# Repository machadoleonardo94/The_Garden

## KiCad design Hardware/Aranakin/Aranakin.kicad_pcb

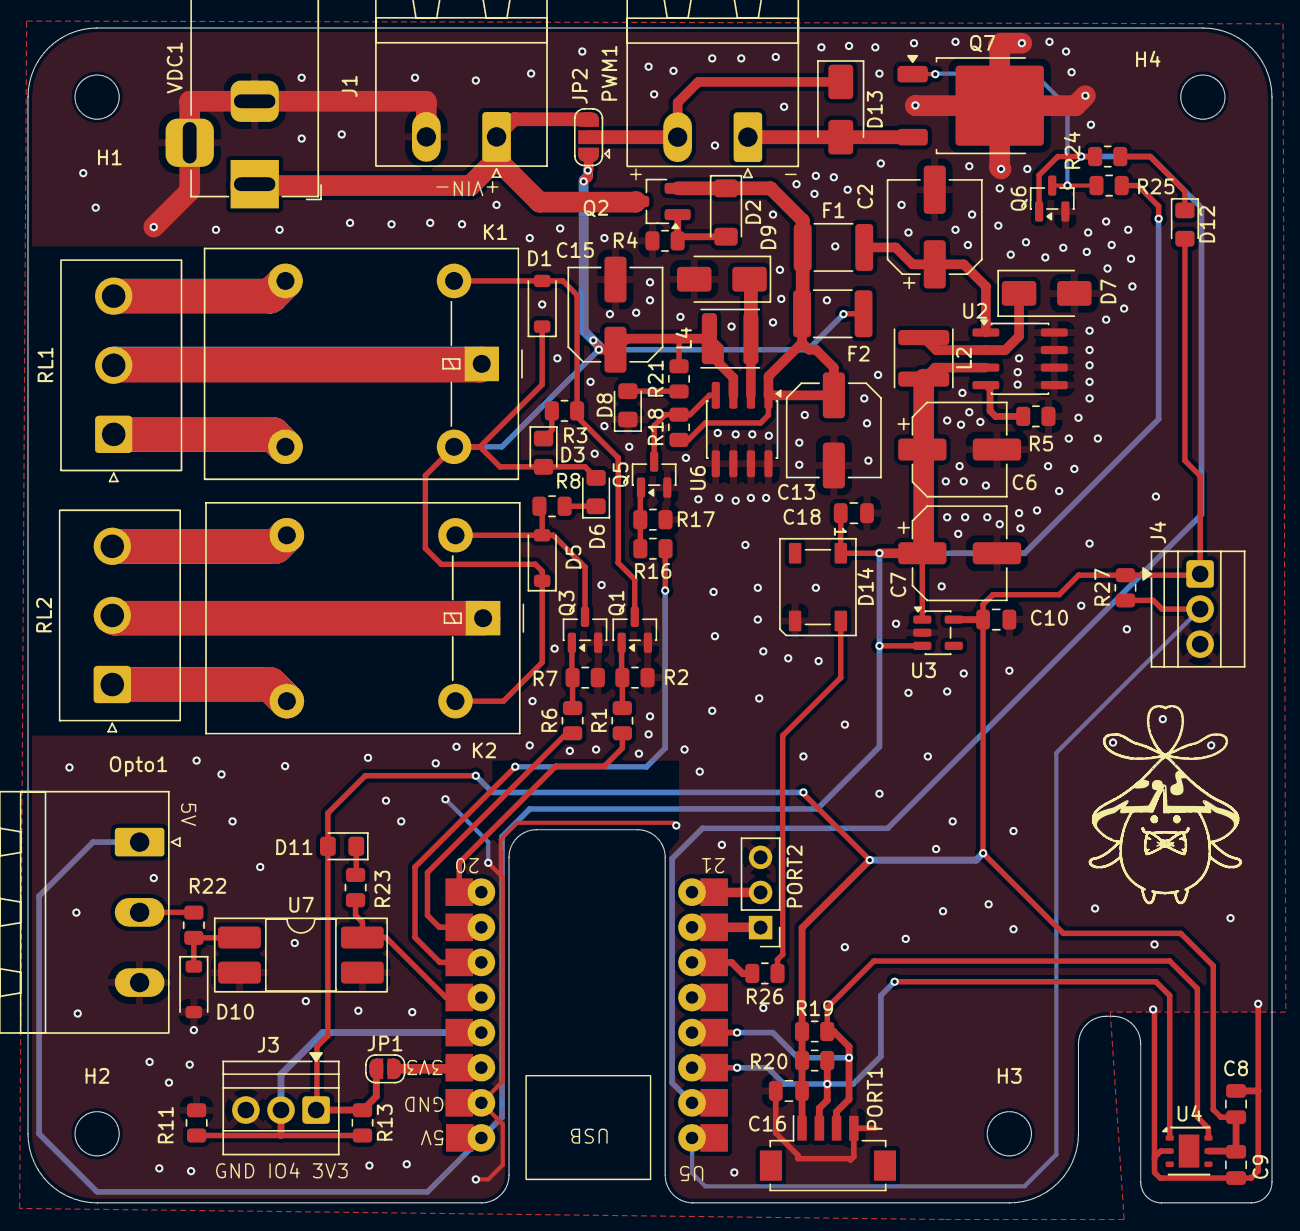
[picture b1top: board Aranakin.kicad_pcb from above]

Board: 2 copper layers, 90.0 x 85.0 mm, 79 parts (0 on the bottom side), 47 nets.

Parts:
C2, C6, C7: 220uF; CP_Elec_6.3x7.7
C8, C10, C16: 10u; C_0805_2012Metric
C9, C18: 100nF; C_0805_2012Metric
C13, C15: 100uF; C_Elec_6.3x7.7
D1, D5, D10: 1N4148W; D_SOD-123
D2: D_Zener; D_MiniMELF
D3, D6: LED_RED; LED_0805_2012Metric_Pad1.15x1.40mm_HandSolder
D7, D9, D13: SS14; D_SMA
D8, D11, D12: LED; LED_0805_2012Metric_Pad1.15x1.40mm_HandSolder
D14: WS2812B; LED_WS2812B_PLCC4_5.0x5.0mm_P3.2mm
F1: 1.1A Polyfuse; Fuse_1812_4532Metric_Pad1.30x3.40mm_HandSolder
F2: Bypass fuse; Fuse_1812_4532Metric_Pad1.30x3.40mm_HandSolder
H1, H2, H3, H4: MountingHole; MountingHole_3.2mm_M3
J1: 5.08-2P-90; PhoenixContact_MSTBA_2,5_2-G-5,08_1x02_P5.08mm_Horizontal
J3: Conn_01x03_Socket; TerminalBlock_Xinya_XY308-2.54-3P_1x03_P2.54mm_Horizontal
J4: 1Wire; TerminalBlock_Xinya_XY308-2.54-3P_1x03_P2.54mm_Horizontal
JP1: SolderJumper_2_Open; SolderJumper-2_P1.3mm_Open_RoundedPad1.0x1.5mm
JP2: SolderJumper_3_Open; SolderJumper-3_P1.3mm_Open_RoundedPad1.0x1.5mm
K1, K2: G5LE-1; Relay_SPDT_Omron-G5LE-1
L2, L4: 33u; L_Sunlord_SWPA4010S
Opto1: Conn_01x03_Pin; PhoenixContact_MSTBA_2,5_3-G-5,08_1x03_P5.08mm_Horizontal
PORT1: Conn_01x04_Socket; Hirose_DF13C_CL535-0404-8-51_1x04-1MP_P1.25mm_Vertical
PORT2: Conn_01x03_Socket; PinHeader_1x03_P2.54mm_Vertical
PWM1: 5.08-2P-90; PhoenixContact_MSTBA_2,5_2-G-5,08_1x02_P5.08mm_Horizontal
Q1, Q3, Q5, Q6: 2N7002K; SOT-23
Q2: PMOS; SOT-23_Handsoldering
Q7: 40N02; TO-252-2
R1, R6, R16, R26: 330; R_0805_2012Metric
R2, R4, R7, R11, R13, R17, R18, R21, R22, R27: 10k; R_0805_2012Metric
R3, R8: 2.2k; R_0805_2012Metric
R5: 100k; R_0805_2012Metric
R19, R20, R25: 2k2; R_0805_2012Metric
R23, R24: 1k; R_0805_2012Metric
RL1, RL2: Conn_01x03_Socket; JST_NV_B03P-NV_1x03_P5.00mm_Vertical
U2: XL1509-5.0; SOIC-8_3.9x4.9mm_P1.27mm
U3: AP2112K-3.3; SOT-23-5
U4: HDC1080; Texas_PWSON-N6
U5: ESP32-C3-Supermini
U6: XL1509-12E1; SOIC-8_3.9x4.9mm_P1.27mm
U7: PC817XI; DIP-4_W8.89mm_SMDSocket_LongPads
VDC1: Barrel_Jack_Switch; BarrelJack_Horizontal

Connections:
1Wire: J4.2, R27.1, U5.1 (GPIO5)
12V_enable: R16.1, U5.11 (GPIO2)
+3.3V: C8.1, C9.2, C10.1, C16.1, D11.2 (A), D12.2 (A), J3.1, J4.1, JP1.1 (A), PORT1.1, R13.1, R19.1, R20.1, R27.2, U3.5 (VOUT), U4.5 (VCC)
+5V: C6.1, C7.1, C18.1, D14.1 (VDD), L2.2, Opto1.1, R25.1, U2.3 (FB), U3.1 (VIN), U3.3 (EN), U5.16 (5V)
ADC: J3.2, R11.2, R13.2, U5.13 (GPIO4)
GND: C2.2, C6.2, C7.2, C8.2, C9.1, C10.2, C13.2, C15.2, C16.2, C18.2, D7.2 (A), D8.1 (K), D9.2 (A), D10.2 (A), D14.3 (VSS), J1.2, J3.3, J4.3, Opto1.3, PORT1.4, PORT2.3, Q1.2 (S), Q3.2 (S), Q5.2 (S), Q6.2 (S), Q7.2 (S), R2.2, R4.2, R5.2, R7.2, R11.1, R17.2, U2.5 (GND), U2.6 (GND), U2.7 (GND), U2.8 (GND), U3.2 (GND), U4.2 (GND), U5.15 (GND), U6.5 (GND), U6.6 (GND), U6.7 (GND), U6.8 (GND), U7.2, U7.3, VDC1.2, VDC1.3
In0: Opto1.2, R22.1
LED_PIN: R26.1, U5.6 (GPIO10)
unnamed: D1.2 (A), K1.2, Q1.3 (D), R3.1
unnamed: D2.2 (A), Q2.1 (G), R4.1
unnamed: D3.1 (K), R3.2
unnamed: D5.2 (A), K2.2, Q3.3 (D), R8.1
unnamed: D6.1 (K), R8.2
unnamed: D7.1 (K), L2.1, U2.2 (OUT)
unnamed: D8.2 (A), R21.1
unnamed: D9.1 (K), L4.1, U6.2 (OUT)
unnamed: D10.1 (K), R22.2, U7.1
unnamed: D11.1 (K), R23.2
unnamed: D12.1 (K), R24.2
unnamed: D13.2 (A), PWM1.1, Q7.3 (D)
unnamed: D13.1 (K), JP2.2 (C), PWM1.2
unnamed: D14.4 (DIN), R26.2
unnamed: JP1.2 (B), U5.14 (3V3)
unnamed: PORT2.1, U5.7 (GPIO20/U0RXD)
unnamed: PORT2.2, U5.8 (GPIO21/U0TXD)
unnamed: Q1.1 (G), R1.2, R2.1
unnamed: Q3.1 (G), R6.2, R7.1
unnamed: Q5.3 (D), R18.2, U6.4 (~EN)
unnamed: Q5.1 (G), R16.2, R17.1
unnamed: Q6.3 (D), Q7.1 (G), R25.2
unnamed: K1.4, RL1.1
unnamed: K1.1, RL1.2
unnamed: K1.3, RL1.3
unnamed: K2.4, RL2.1
unnamed: K2.1, RL2.2
unnamed: K2.3, RL2.3
unnamed: C2.1, F1.2, U2.1 (VIN)
Opto: R23.1, U5.12 (GPIO3), U7.4
PWR_EN: R5.1, U2.4 (~EN)
RELAY0_PIN: R1.1, U5.9 (GPIO0)
RELAY1_PIN: R6.1, U5.10 (GPIO1)
SCL: PORT1.3, R19.2, U4.6 (SCL), U5.4 (GPIO8)
SDA: PORT1.2, R20.2, U4.1 (SDA), U5.3 (GPIO7)
VCC: C13.1, D2.1 (K), F1.1, F2.1, Q2.2 (S), R18.1, U6.1 (VIN)
Vin: J1.1, JP2.3 (B), Q2.3 (D), VDC1.1
openDrain: Q6.1 (G), R24.1, U5.2 (GPIO6)
relayPWR: C15.1, D1.1 (K), D3.2 (A), D5.1 (K), D6.2 (A), F2.2, JP2.1 (A), K1.5, K2.5, L4.2, R21.2, U6.3 (FB)

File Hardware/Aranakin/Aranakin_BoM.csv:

Reference,Qty,Value,Footprint
"C2,C6,C7",3,220uF,Capacitor_SMD:CP_Elec_6.3x7.7
"C8,C10,C16",3,10u,Capacitor_SMD:C_0805_2012Metric
"C9,C18",2,100nF,Capacitor_SMD:C_0805_2012Metric
"C13,C15",2,100uF,Capacitor_SMD:C_Elec_6.3x7.7
"D1,D5,D10",3,1N4148W,Diode_SMD:D_SOD-123
D2,1,D_Zener,Diode_SMD:D_MiniMELF
"D3,D6",2,LED_RED,LED_SMD:LED_0805_2012Metric_Pad1.15x1.40mm_HandSolder
"D7,D9,D13",3,SS14,Diode_SMD:D_SMA
"D8,D11,D12",3,LED,LED_SMD:LED_0805_2012Metric_Pad1.15x1.40mm_HandSolder
D14,1,WS2812B,LED_SMD:LED_WS2812B_PLCC4_5.0x5.0mm_P3.2mm
F1,1,1.1A Polyfuse,Fuse:Fuse_1812_4532Metric_Pad1.30x3.40mm_HandSolder
F2,1,Bypass fuse,Fuse:Fuse_1812_4532Metric_Pad1.30x3.40mm_HandSolder
"J1,PWM1",2,5.08-2P-90,"Connector_Phoenix_MSTB:PhoenixContact_MSTBA_2,5_2-G-5,08_1x02_P5.08mm_Horizontal"
J3,1,Conn_01x03_Socket,TerminalBlock:TerminalBlock_Xinya_XY308-2.54-3P_1x03_P2.54mm_Horizontal
J4,1,1Wire,TerminalBlock:TerminalBlock_Xinya_XY308-2.54-3P_1x03_P2.54mm_Horizontal
"K1,K2",2,G5LE-1,Relay_THT:Relay_SPDT_Omron-G5LE-1
"L2,L4",2,33u,Inductor_SMD:L_Sunlord_SWPA4010S
Opto1,1,Conn_01x03_Pin,"Connector_Phoenix_MSTB:PhoenixContact_MSTBA_2,5_3-G-5,08_1x03_P5.08mm_Horizontal"
PORT1,1,Conn_01x04_Socket,Connector_Hirose:Hirose_DF13C_CL535-0404-8-51_1x04-1MP_P1.25mm_Vertical
PORT2,1,Conn_01x03_Socket,Connector_PinHeader_2.54mm:PinHeader_1x03_P2.54mm_Vertical
"Q1,Q3,Q5,Q6",4,2N7002K,Package_TO_SOT_SMD:SOT-23
Q2,1,PMOS,Package_TO_SOT_SMD:SOT-23_Handsoldering
Q7,1,40N02,Package_TO_SOT_SMD:TO-252-2
"R1,R6,R16,R26",4,330R,Resistor_SMD:R_0805_2012Metric
"R2,R4,R7,R11,R13,R17,R18,R21,R22,R27",10,10k,Resistor_SMD:R_0805_2012Metric
"R3,R8",2,2.2k,Resistor_SMD:R_0805_2012Metric
R5,1,100k,Resistor_SMD:R_0805_2012Metric
"R19,R20,R25",3,2k2,Resistor_SMD:R_0805_2012Metric
"R23,R24",2,1k,Resistor_SMD:R_0805_2012Metric
"RL1,RL2",2,Conn_01x03_Socket,Connector_JST:JST_NV_B03P-NV_1x03_P5.00mm_Vertical
U2,1,XL1509-5.0,Package_SO:SOIC-8_3.9x4.9mm_P1.27mm
U3,1,AP2112K-3.3,Package_TO_SOT_SMD:SOT-23-5
U4,1,HDC1080,Package_SON:Texas_PWSON-N6
U5,1,ESP32-C3-Supermini,Custom_Footprints:ESP32-C3-Supermini
U6,1,XL1509-12E1,Package_SO:SOIC-8_3.9x4.9mm_P1.27mm
U7,1,PC817XI,Package_DIP:DIP-4_W8.89mm_SMDSocket_LongPads
VDC1,1,Barrel_Jack_Switch,Connector_BarrelJack:BarrelJack_Horizontal

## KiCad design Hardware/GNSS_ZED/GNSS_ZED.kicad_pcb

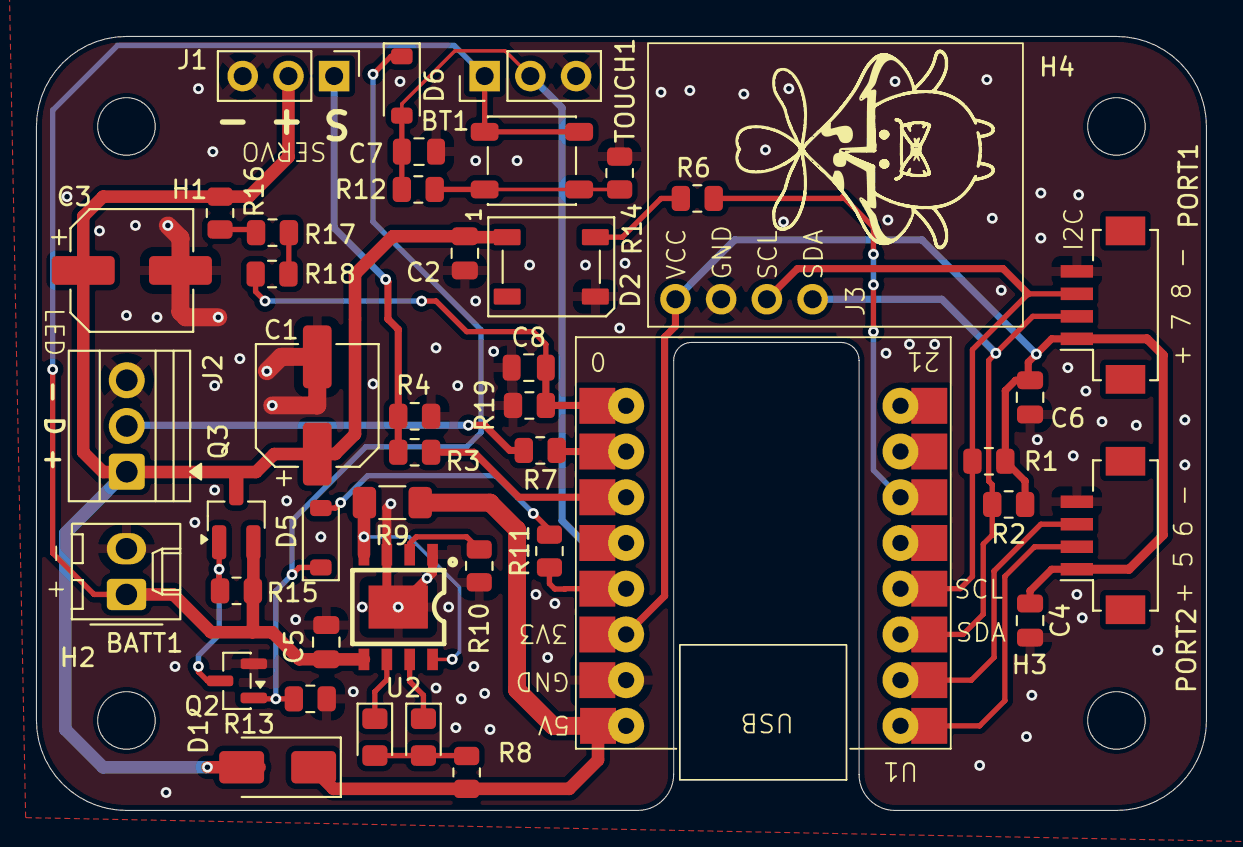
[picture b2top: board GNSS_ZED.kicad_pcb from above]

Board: 2 copper layers, 65.0 x 43.0 mm, 48 parts (0 on the bottom side), 29 nets.

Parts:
BATT1: Conn_01x02_Socket; Molex_KK-254_AE-6410-02A_1x02_P2.54mm_Vertical
BT1: SW_Push; SW_SPST_PTS647_Sx38
C1, C3: 220uF; CP_Elec_6.3x7.7
C2, C7, C8: 100nF; C_0805_2012Metric
C4, C5, C6: 10u; C_0805_2012Metric
D1: SS14; D_SMA
D2: WS2812B; LED_WS2812B_PLCC4_5.0x5.0mm_P3.2mm
D3: LED_BLUE; LED_0805_2012Metric_Pad1.15x1.40mm_HandSolder
D4: LED_RED; LED_0805_2012Metric_Pad1.15x1.40mm_HandSolder
D5, D6: 1N4148W; D_SOD-123
H1, H2, H3, H4: MountingHole; MountingHole_3.2mm_M3
J1: Conn_01x03_Socket; PinHeader_1x03_P2.54mm_Vertical
J2: Conn_01x03_Socket; TerminalBlock_Xinya_XY308-2.54-3P_1x03_P2.54mm_Horizontal
J3: Conn_01x04_Socket; MPU6050
PORT1, PORT2: Conn_01x04_Socket; Hirose_DF13C_CL535-0404-8-51_1x04-1MP_P1.25mm_Vertical
Q2: 2N7002K; SOT-23
Q3: PMOS; SOT-23_Handsoldering
R1, R2, R8, R10, R12: 2.2k; R_0805_2012Metric
R3, R6, R7, R11: 330; R_0805_2012Metric
R4, R13: 10k; R_0805_2012Metric
R9: 0R22; R_1206_3216Metric_Pad1.30x1.75mm_HandSolder
R14, R15, R16, R17, R18, R19: 100k; R_0805_2012Metric
TOUCH1: Conn_01x03_Socket; PinHeader_1x03_P2.54mm_Vertical
U1: ESP32-C3-Supermini
U2: TP4056; ESOP-8_L4.9-W3.9-P1.27-LS6.0-BL-EP

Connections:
+3.3V: C4.1, C6.1, J3.1, PORT1.1, PORT2.1, R1.1, R2.1, U1.14 (3V3)
+5V: D1.1 (K), R8.1, R9.1, U1.16 (5V)
+BATT: BATT1.1, BT1.1, C5.1, Q3.2 (S), R15.2, TOUCH1.1, U2.5 (BAT)
ADC1_0: C8.2, R18.1, R19.1, U1.9 (GPIO0)
Button_GPIO: C7.2, D6.2 (A), R12.2, TOUCH1.2, U1.12 (GPIO3)
GND: BATT1.2, C1.2, C2.2, C3.2, C4.2, C5.2, C6.2, C7.1, C8.1, D2.3 (VSS), J1.3, J2.3, J3.2, PORT1.4, PORT2.4, Q2.2 (S), R4.2, R10.1, R13.2, R14.1, R19.2, TOUCH1.3, U1.15 (GND), U2.1 (TEMP), U2.3 (GND), U2.9 (EP)
GPIO_5: PORT2.2, U1.1 (GPIO5)
GPIO_6: PORT2.3, U1.2 (GPIO6)
unnamed: BT1.2, R12.1, R14.2
unnamed: D2.4 (DIN), R6.2
unnamed: D3.2 (A), D4.2 (A), R8.2
unnamed: D3.1 (K), U2.6 (STDBY#)
unnamed: D4.1 (K), U2.7 (CHRG#)
unnamed: D5.2 (A), R11.2
unnamed: D5.1 (K), D6.1 (K), Q2.1 (G), R13.1
unnamed: J1.1, R3.2, R4.1
unnamed: J2.2, R7.2
unnamed: Q2.3 (D), Q3.1 (G), R15.1
unnamed: R16.1, R17.2
unnamed: R17.1, R18.2
unnamed: R9.2, U2.4 (VCC), U2.8 (CE)
unnamed: R10.2, U2.2 (PROG)
SCL: J3.3, PORT1.3, R1.2, U1.4 (GPIO8)
SDA: J3.4, PORT1.2, R2.2, U1.3 (GPIO7)
Servo_out: R3.1, U1.11 (GPIO2)
Status_LED: R6.1, U1.6 (GPIO10)
Strip_out: R7.1, U1.10 (GPIO1)
V_REG: C1.1, C2.1, C3.1, D1.2 (A), D2.1 (VDD), J1.2, J2.1, Q3.3 (D), R16.2
latch_enable: R11.1, U1.13 (GPIO4)

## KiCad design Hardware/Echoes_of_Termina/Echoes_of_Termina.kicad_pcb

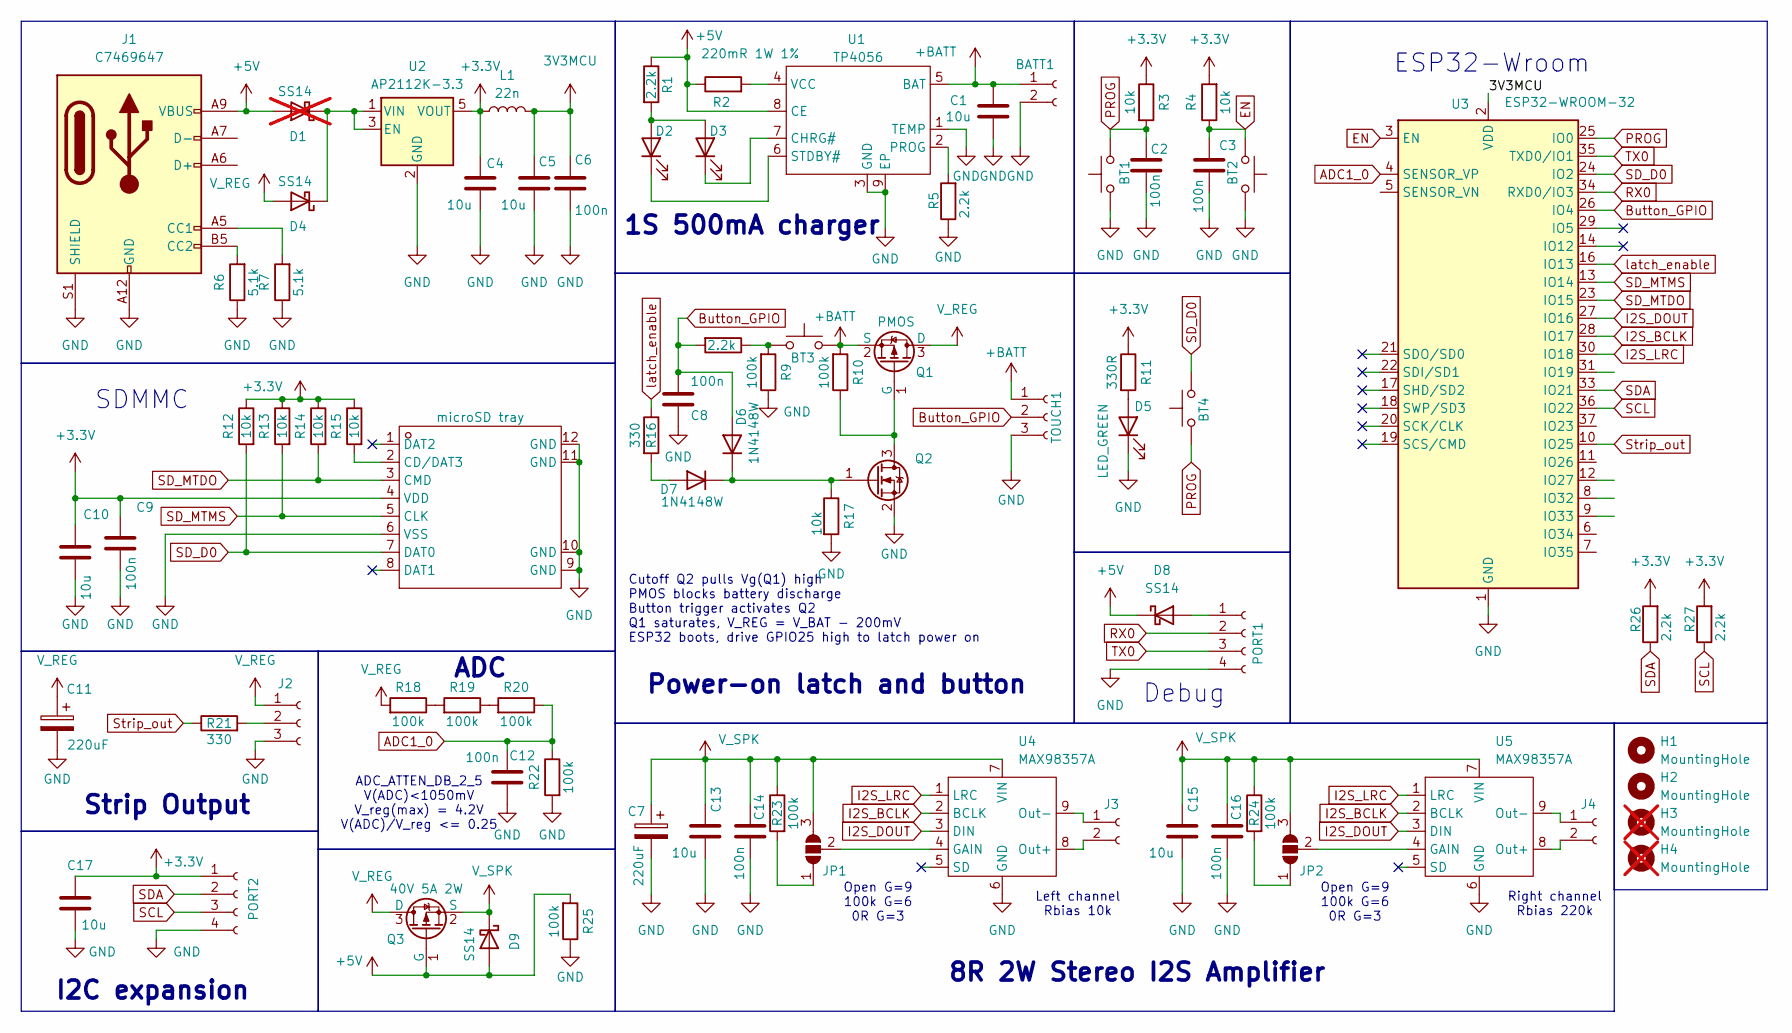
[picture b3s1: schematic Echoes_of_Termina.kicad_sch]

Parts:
BATT1: Conn_01x02_Socket; Molex_KK-254_AE-6410-02A_1x02_P2.54mm_Vertical; LCSC C49023803
BT1, BT2, BT3, BT4: SW_Push; SW_SPST_PTS647_Sx38; LCSC C2888502
C1, C4, C5, C10, C13, C15, C17: 10u; C_0805_2012Metric; LCSC C162422
C2, C3, C6, C9: 100n; C_0805_2012Metric; LCSC C49678
C7, C11: 220uF; CP_Elec_8x10.5; Mfr. Part Number 35TKV220M8X10.5; LCSC C2162971
C8, C12, C14, C16: 100n; C_0805_2012Metric; Mfr. Part Number CC0805KRX7R9BB104; LCSC C49678
D1: SS14; D_SMA; LCSC C2480; not fitted
D2: LED_BLUE; LED_0805_2012Metric_Pad1.15x1.40mm_HandSolder; LCSC C965817
D3: LED_RED; LED_0805_2012Metric_Pad1.15x1.40mm_HandSolder; LCSC C84256
D4, D8, D9: SS14; D_SMA; LCSC C2480
D5: LED_GREEN; LED_0805_2012Metric_Pad1.15x1.40mm_HandSolder; LCSC C84256
D6, D7: 1N4148W; D_SOD-123; Mfr. Part Number 1N4148W-7-F; LCSC C83528
H1, H2: MountingHole; MountingHole_3.2mm_M3
H3, H4: MountingHole; MountingHole_3.2mm_M3; not fitted
J1: USB_C_Receptacle_USB2.0_8P; USB-C-SMD_GT-USB-7101A; LCSC C7469647
J2: Conn_01x03_Socket; TerminalBlock_Xinya_XY308-2.54-3P_1x03_P2.54mm_Horizontal
J3, J4: Conn_01x02_Socket; JST_GH_BM02B-GHS-TBT_1x02-1MP_P1.25mm_Vertical
JP1, JP2: SolderJumper_3_Open; SolderJumper-3_P1.3mm_Open_RoundedPad1.0x1.5mm
L1: 22n; L_0805_2012Metric; LCSC C108962
PORT1, PORT2: Conn_01x04_Socket; Hirose_DF13C_CL535-0404-8-51_1x04-1MP_P1.25mm_Vertical; LCSC C7433470
Q1, Q3: PMOS; SOT-23_Handsoldering; LCSC C42456992
Q2: 2N7002K; SOT-23; LCSC C65189
R1, R5, R8, R26, R27: 2.2k; R_0805_2012Metric; LCSC C17520
R2: 220mR 1W 1%; R_1206_3216Metric_Pad1.30x1.75mm_HandSolder; Mfr. Part Number RLH12FTCR220; LCSC C2683384
R3, R4, R12, R13, R14, R15, R17: 10k; R_0805_2012Metric; LCSC C17414
R6, R7: 5.1k; R_0805_2012Metric; LCSC C27834
R9, R10, R18, R19, R20, R22, R23, R24, R25: 100k; R_0805_2012Metric; LCSC C149504
R11: 330R; R_0805_2012Metric; LCSC C17630
R16, R21: 330; R_0805_2012Metric; LCSC C17630
TF1: microSD tray; TF-SMD_TF-CARD-XG8P-H1.5; LCSC C7529392
TOUCH1: Conn_01x03_Socket; PinHeader_1x03_P2.54mm_Vertical
U1: TP4056; ESOP-8_L4.9-W3.9-P1.27-LS6.0-BL-EP; LCSC Part Name 1A锂电池充电IC
U2: AP2112K-3.3; SOT-23-5; LCSC C51118
U3: ESP32-WROOM-32; ESP32-WROOM-32U; LCSC C2980301
U4, U5: MAX98357A; LCSC C910544

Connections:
3V3MCU: C5.1, C6.1, L1.2, U3.2 (VDD)
+3.3V: C4.1, C9.2, C10.1, C17.1, L1.1, PORT2.1, R3.1, R4.2, R11.1, R12.1, R13.1, R14.1, R15.1, R26.2, R27.2, TF1.4 (VDD), U2.5 (VOUT)
+5V: D1.2 (A), D8.1 (K), D9.2 (A), J1.A9 (VBUS), J1.B9 (VBUS), Q3.1 (G), R1.1, R2.1, R25.2, U1.8 (CE)
+BATT: BATT1.1, BT3.1, C1.1, Q1.2 (S), R10.2, TOUCH1.1, U1.5 (BAT)
ADC1_0: C12.2, R20.1, R22.1, U3.4 (SENSOR_VP)
Button_GPIO: C8.2, D6.2 (A), R8.2, TOUCH1.2, U3.26 (IO4)
EN: BT2.2, C3.1, R4.1, U3.3 (EN)
GND: BATT1.2, BT1.1, BT2.1, C1.2, C2.2, C3.2, C4.2, C5.2, C6.2, C7.2, C8.1, C9.1, C10.2, C11.2, C12.1, C13.2, C14.1, C15.2, C16.1, C17.2, D5.1 (K), J1.A12 (GND), J1.B12 (GND), J1.S1 (SHIELD), J2.3, PORT1.4, PORT2.4, Q2.2 (S), R5.1, R6.1, R7.1, R9.1, R17.2, R22.2, R25.1, TF1.6 (VSS), TF1.9 (GND), TF1.10 (GND), TF1.11 (GND), TF1.12 (GND), TOUCH1.3, U1.1 (TEMP), U1.3 (GND), U1.9 (EP), U2.2 (GND), U3.1 (GND), U3.15 (GND), U3.38 (GND), U3.39 (GND), U4.6 (GND), U5.6 (GND)
I2S_BCLK: U3.28 (IO17), U4.2 (BCLK), U5.2 (BCLK)
I2S_DOUT: U3.27 (IO16), U4.3 (DIN), U5.3 (DIN)
I2S_LRC: U3.30 (IO18), U4.1 (LRC), U5.1 (LRC)
unnamed: BT3.2, R8.1, R9.2
unnamed: D2.2 (A), D3.2 (A), R1.2
unnamed: D2.1 (K), U1.6 (STDBY#)
unnamed: D3.1 (K), U1.7 (CHRG#)
unnamed: D1.1 (K), D4.1 (K), U2.1 (VIN), U2.3 (EN)
unnamed: D5.2 (A), R11.2
unnamed: D6.1 (K), D7.1 (K), Q2.1 (G), R17.1
unnamed: D7.2 (A), R16.2
unnamed: D8.2 (A), PORT1.1
unnamed: J1.A5 (CC1), R7.2
unnamed: J1.B5 (CC2), R6.2
unnamed: J2.2, R21.2
unnamed: J3.1, U4.9 (Out-)
unnamed: J3.2, U4.8 (Out+)
unnamed: J4.1, U5.9 (Out-)
unnamed: J4.2, U5.8 (Out+)
unnamed: JP1.1 (A), R23.2
unnamed: JP1.2 (C), U4.4 (GAIN)
unnamed: JP2.1 (A), R24.2
unnamed: JP2.2 (C), U5.4 (GAIN)
unnamed: Q1.1 (G), Q2.3 (D), R10.1
unnamed: R18.1, R19.2
unnamed: R19.1, R20.2
unnamed: R15.2, TF1.2 (CD/DAT3)
unnamed: R5.2, U1.2 (PROG)
unnamed: R2.2, U1.4 (VCC)
PROG: BT1.2, BT4.2, C2.1, R3.2, U3.25 (IO0)
RX0: PORT1.2, U3.34 (RXD0/IO3)
SCL: PORT2.3, R27.1, U3.36 (IO22)
SDA: PORT2.2, R26.1, U3.33 (IO21)
SD_D0: BT4.1, R12.2, TF1.7 (DAT0), U3.24 (IO2)
SD_MTDO: R14.2, TF1.3 (CMD), U3.23 (IO15)
SD_MTMS: R13.2, TF1.5 (CLK), U3.13 (IO14)
Strip_out: R21.1, U3.10 (IO25)
TX0: PORT1.3, U3.35 (TXD0/IO1)
V_REG: C11.1, D4.2 (A), J2.1, Q1.3 (D), Q3.3 (D), R18.2
V_SPK: C7.1, C13.1, C14.2, C15.1, C16.2, D9.1 (K), JP1.3 (B), JP2.3 (B), Q3.2 (S), R23.1, R24.1, U4.7 (VIN), U5.7 (VIN)
latch_enable: R16.1, U3.16 (IO13)

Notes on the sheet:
Strip Output
Right channel Rbias 220k
Open G=9 100k G=6 0R G=3
Power-on latch and button
8R 2W Stereo I2S Amplifier
ADC_ATTEN_DB_2_5 V(ADC)<1050mV V_reg(max) = 4.2V V(ADC)/V_reg <= 0.25
ADC
SDMMC
Left channel Rbias 10k
I2C expansion
Cutoff Q2 pulls Vg(Q1) high PMOS blocks battery discharge Button trigger activates Q2 Q1 saturates, V_REG = V_BAT - 200mV ESP32 boots, drive GPIO25 high to latch power on
Debug
ESP32-Wroom
1S 500mA charger

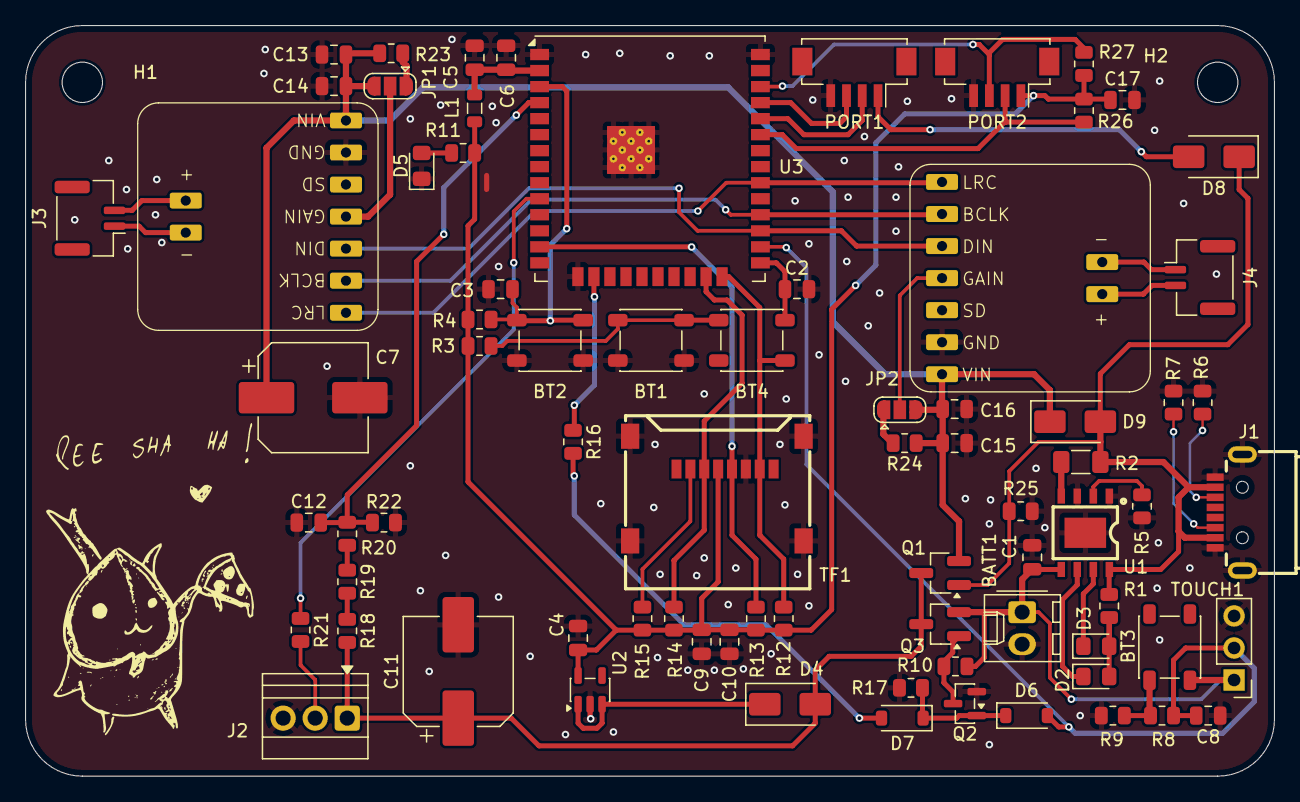
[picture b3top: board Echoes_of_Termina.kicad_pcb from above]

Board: 2 copper layers, 99.0 x 59.5 mm, 78 parts (0 on the bottom side), 49 nets.

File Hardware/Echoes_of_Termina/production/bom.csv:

Designator,Footprint,Quantity,Value,LCSC Part #
"BT1, BT2, BT3, BT4",SW_SPST_PTS647_Sx38,4,SW_Push,C2888502
"C1, C10, C13, C15, C17, C4, C5",0805,7,10u,C162422
"C11, C7",CP_Elec_8x10.5,2,220uF,C2162971
"C12, C14, C16, C2, C3, C6, C8, C9",0805,8,100n,C49678
D2,0805,1,LED_BLUE,C965817
D3,0805,1,LED_RED,C84256
"D4, D8, D9",D_SMA,3,SS14,C2480
D5,0805,1,LED_GREEN,C84256
"D6, D7",D_SOD-123,2,1N4148W,C83528
J1,USB-C-SMD_GT-USB-7101A,1,USB_C_Receptacle_USB2.0_8P,C7469647
J2,TerminalBlock_Xinya_XY308-2.54-3P_1x03_P2.54mm_Horizontal,1,Conn_01x03_Socket,
"J3, J4",JST_GH_BM02B-GHS-TBT_1x02-1MP_P1.25mm_Vertical,2,Conn_01x02_Socket,
L1,0805,1,22n,C108962
"PORT1, PORT2",Hirose_DF13C_CL535-0404-8-51_1x04-1MP_P1.25mm_Vertical,2,Conn_01x04_Socket,C7433470
"Q1, Q3",SOT-23_Handsoldering,2,PMOS,C42456992
Q2,SOT-23,1,2N7002K,C65189
"R1, R26, R27, R5, R8",0805,5,2.2k,C17520
"R10, R18, R19, R20, R22, R23, R24, R25, R9",0805,9,100k,C149504
R11,0805,1,330R,C17630
"R12, R13, R14, R15, R17, R3, R4",0805,7,10k,C17414
"R16, R21",0805,2,330,C17630
R2,1206,1,220mR 1W 1%,C2683384
"R6, R7",0805,2,5.1k,C27834
TF1,TF-SMD_TF-CARD-XG8P-H1.5,1,microSD tray,C7529392
TOUCH1,PinHeader_1x03_P2.54mm_Vertical,1,Conn_01x03_Socket,
U1,ESOP-8_L4.9-W3.9-P1.27-LS6.0-BL-EP,1,TP4056,C382139
U2,SOT-23-5,1,AP2112K-3.3,C51118
U3,ESP32-WROOM-32U,1,ESP32-WROOM-32,C2980301
"U4, U5",MAX98357A,2,MAX98357A,C910544

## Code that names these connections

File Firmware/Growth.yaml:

esphome:
  name: shruberry
  comment: Soil and air monitor node
  friendly_name: Shruberry

esp32:
  board: esp32-c3-devkitm-1
  flash_size: 4MB
  cpu_frequency: 160MHz
  framework:
    type: arduino

# Enable logging
logger:

# Enable Home Assistant API
api:
  encryption:
    key: "RdF1G7t8J7YeDF7+U37MlYBPoCRI7uNhtiTiJ7lXKgE="

ota:
  - platform: esphome
    password: "0afd624b144523bce53f36563bb89966"

# WiFi configuration with fallback mechanisms
wifi:
  ssid: "AleoExpress"
  password: Engenharia01
  ap:
    ssid: "Shruberry_AP"
    password: ""

# Add captive portal for AP mode
captive_portal:

# Enable web server for status page
web_server:
  port: 80
  local: true
  version: 3

# Define I2C bus
i2c:
  id: bus_i2c
  sda: GPIO7
  scl: GPIO8
  scan: true
  frequency: 400kHz

#MARK: Buttons
binary_sensor:
  - platform: gpio
    pin:
      number: GPIO9
      mode:
        input: true
        pullup: true
      inverted: true
    name: "Button A"
    id: button_a
    icon: mdi:gesture-tap
    on_press:
      - logger.log: "Button A pressed"

switch:
  - platform: factory_reset
    name: Restart with Factory Default Settings
  #MARK: Relay Enable
  - platform: gpio
    pin: GPIO2
    name: "Relay Enable"
    id: relay_switch
    device_class: switch
    icon: mdi:power-plug
    restore_mode: RESTORE_DEFAULT_OFF
  #MARK: Schedule Toggle
  - platform: template
    name: "Outlet 1 Schedule Enabled"
    id: outlet1_schedule_enabled
    icon: mdi:calendar-clock
    restore_mode: RESTORE_DEFAULT_OFF
    optimistic: true

  #MARK: Relays
  - platform: gpio
    id: relay0
    name: "Outlet 1"
    device_class: outlet
    icon: "mdi:power-socket-ch"
    internal: false
    restore_mode: RESTORE_DEFAULT_OFF
    pin: GPIO0
  - platform: gpio
    id: relay1
    name: "Outlet 2"
    device_class: outlet
    icon: "mdi:power-socket-ch"
    internal: false
    restore_mode: RESTORE_DEFAULT_OFF
    pin: GPIO1

# Status sensors
sensor:
  - platform: wifi_signal
    name: "WiFi Signal"
    update_interval: 60s

  - platform: uptime
    name: "Uptime"
    update_interval: 60s

  - platform: adc
    pin: GPIO4
    name: "Soil"
    update_interval: 10s
    attenuation: 11db
    #filters:
    #  - multiply: 3.3

# Define text sensors for device status
text_sensor:
  - platform: wifi_info
    ip_address:
      name: "IP Address"
    ssid:
      name: "Connected SSID"
    bssid:
      name: "Connected BSSID"
      internal: true
    mac_address:
      name: "MAC Address"
      internal: true

# Define buttons for device control
button:
  - platform: restart
    name: "Restart Node"

# Add a time component to keep track of time
time:
  - platform: homeassistant
    id: homeassistant_time
    on_time_sync:
      then:
        - logger.log: "Time synchronized with Home Assistant"
    on_time:
      #MARK: Outlet 1 Schedule — fires every minute
      - seconds: 0
        minutes: "*"
        hours: "*"
        then:
          - lambda: |-
              if (!id(outlet1_schedule_enabled).state) return;
              auto t = id(homeassistant_time).now();
              if (!t.is_valid()) return;
              int on_h = 0, on_m = 0, off_h = 0, off_m = 0;
              sscanf(id(outlet1_on_time).state.c_str(),  "%d:%d", &on_h,  &on_m);
              sscanf(id(outlet1_off_time).state.c_str(), "%d:%d", &off_h, &off_m);
              if (t.hour == on_h && t.minute == on_m) {
                id(relay0).turn_on();
                ESP_LOGI("schedule", "Outlet 1 turned ON at %d:%02d", t.hour, t.minute);
              }
              if (t.hour == off_h && t.minute == off_m) {
                id(relay0).turn_off();
                ESP_LOGI("schedule", "Outlet 1 turned OFF at %d:%02d", t.hour, t.minute);
              }

#MARK: Outlet 1 Schedule Configuration
text:
  - platform: template
    name: "Outlet 1 Turn On Time"
    id: outlet1_on_time
    mode: text
    max_length: 5
    initial_value: "06:00"
    restore_value: true
    optimistic: true
    icon: mdi:clock-start
  - platform: template
    name: "Outlet 1 Turn Off Time"
    id: outlet1_off_time
    mode: text
    max_length: 5
    initial_value: "22:00"
    restore_value: true
    optimistic: true
    icon: mdi:clock-end

# Add persistent storage for configuration
globals:
  - id: config_version
    type: int
    restore_value: yes
    initial_value: "1"

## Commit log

2026-03-03 Basic hardware for C3 plant monitor
2026-03-04 Minor hardware update
2026-03-04 Added base ESPhome firmware
2026-03-04 Added base firmware
2026-03-04 Hardware update
2026-03-05 Added first layout and fabrication files
2026-03-06 Fabrication files update
    Removed copper fill on antenna zone.
    In future versions, put relay far away from ESP.
    Move fast and break things
2026-03-26 Added BoM PDF
2026-04-15 Added timekeeping tingamajig
2026-04-17 Added Echoes of Termina base hardware
2026-04-20 First PCB sketch for Echoes of Termina
2026-04-21 Echoes layout for revision before fabrication
2026-06-05 Add GNSS prototype
2026-06-29 GNSS_ZED update
